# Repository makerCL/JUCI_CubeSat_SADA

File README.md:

## CubeSat Solar Array Drive - Cal Poly Senior Project

This repository presents the development and proposed design of a deployable Solar Array Drive Assembly that could be flown on space-bound CubeSat missions. Our project addresses the need for reliable sources of power in spacecraft and other missions beyond the Earth's atmosphere. Our goal is to create a two degree of freedom SADA, including the passive retainment, deployment, and axial rotation of a solar array to track the sun during the CubeSat’s orbit. It will have the ability to be easily adapted and integrated into other CubeSat builds but does not include other subsystems necessary for full satellite. The scope includes three main areas: the design and manufacture of a 90-degree locking hinge that allows multiple solar arrays to deploy from the stored launch state, the controlled axial rotation of the deployed panels, and the electronics necessary to manage these features with the potential for sun tracking algorithms. 

Subsystem Managers:
- Miles - Electronics
- Gavin - Software
- James - Project Management
- Kory  - Mechanical
- Jose  - Mechanical

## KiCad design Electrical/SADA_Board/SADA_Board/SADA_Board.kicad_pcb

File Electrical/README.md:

This file details the electrical subsystems
Author: Miles Alderman

##Boards:
- Photodiode Breakout: used for sun sensing with one connected to each solar array
- Pico Shield: Peripherals and connection points that interfaces with a Raspberry Pi Pico

##Accessing the Files
- all project files are in Kicad version 6, which the use will need to use to view them
- Digikey library was imported, available at https://forum.digikey.com/t/importing-the-digi-key-kicad-library-into-kicad-5-0-0/4075
- Custom schematic symbols and footprints are in the "KiCad Libs" folder. These will need to be imported

#SADA Board

##Description
The "SADA BOARD" encompasses all the functionality necessary for the Solar Array Drive Assembly and its components. It would interface with a "Systems Board" through a protocol like I2C or CAN.

##Functionality
- Voltage regulator accepts between 3.7 to 4.2V from an external power supply, which represents a single parallel group of Lithium Ion cells, as would like be present in a CubeSat since about 66% of nano and pico scale satellites implement them.(Bouwmeester and Guo). A battery and battery management system is out of scope for this project.
- Nichrome Wire burner: to burn the fishing line that passively retains the spring-loaded solar arrays, we use Nichrome burn wire. This is necessary since the satellite must be powered off during launch. There are pins used to control the burn signal, one of which is the enable for the PMIC, the other of which controls a Mosfet for connecting power to the Nichrome. In some tests, we found that when the system was powered up from its launch state, if the power supply was turned on with a direct connection to the wire it heated it slower, resulting in less reliable deployment. By having a transistor, we can allow the PMIC to become fully stable, and then open it to heat the wire. This PMIC can then be disable to save power after the wire is burnt. Our tests foudn that about 1.5A was the minimum current to heat the wire enough to cleanly burn the fishing line.
- Attitude Determination Diodes: since in a full CubeSat build there would need to be orientation photodiodes on each corner, the peripherals are provided to do so. This includes a MUX to an ADC channel of the MCU to take this measurement.
    - The photodiodes were connected in reverse bias to the inverting input of an op amp. To take a reading with good resolution, this tiny current must be amplified before reaching an ADC. Transconductance amplifiers are a way to do this, connecting the photodiode to the inverting input of an op-amp, the non-inverting input to ground, and placing a feedback resistor from inverting input to output. A capacitor in parallel with the feedback resistor adds stability by acting as a voltage buffer. Capacitance in the photodiode combined with the feedback resistor naturally create a low pass filter as well. The output voltage of the amplifier can then be connected to an ADC channel of the MCU. The voltage sent to the ADC channel is equal to the photodiode current times the feedback resistor plus the offset voltage at the non-inverting input.
    - It is important to verify the photodiode current is at least an order of magnitude more than the input bias current of the op amp, which roughly doubles with ever 10 deg C increase in temperature.
- Stepper Motor Drivers: Since the stepper motors for axial rotation of the arrays need to be driven from the MCU, a Darlington Transistor array is used to accomplish this. This allows the small current of the MCU GPIO to drive the much higher current needed by a stepper, taken from the 5V supply. Stepper motors are precise, but very power hungry due to _________, so we decided to have MOSFETS that can disconnect from power for when the steppers are not actively changed. This does eliminate some functionality of the steppers, such as fractional stepping, but the resolution of that is far greater than our sensing method's, and thus we couldn't take advantage of it anywyas.
- Breakout board connectors: connectors to the Photodiode Breakout Board are implemented for 2 MUX pins, an ADC channel, power and ground

##Design Considerations 
For full information, please see current design report in the parent folder of the repository. Some key details are listed below
- Were not able to use a "space grade" MCU since they are far too expensive for the price point of this project. We therefore are trying to adapt consumer grade MCUs to fit the needs of this project. This would only protect against total radiation experienced from low energy particles, and not against bit flips. In the systems board, TMR would likely be used. 
- Since this is a prototype and will not be launched into space, we aren't going through the rad hardening. It would be silly to spend extra money for a more specific MCU that wouldn’t work anyways. All the other common MCUs have similar temperature ranges besides the ESP32, although its is still not within range of what we expect a CubeSat to encounter
- Dual Modular Redundancy for these systems?
- In a full system, the battery system would output between about 3.6 - 4.2V if a lithium ion cell chemistry was used. We need to step that down to 3.3V for the RP2040. We chose to use an LDO to power the MCU despite them being less efficient than switching regulators since when the LDOs will use less power when considering the high amount of sleep time of the MCU.
- We decided to use stepper motors despite them being very power hungry. Stepper motors invert  the "locked rotor" issue of dc motors, stepping between locked rotor positions. This means that when the motor is not moving, the coils are still fully energized. This is bad for a CubeSat, where power is extremely scarce. To get around this issue while still utilizing the positional accuracy of stepper motors, we can step the motor and then immediately disconnect the power line so that it stops drawing current. Since the cores of the motor are permenant magnets, the motor remains in the last position even when the motor is off, as long as we do not depend on any partial-stepping functions. 
- USB implemented for the development process, but isn't necessary on a deployed system. It allows the engineer to set it up as a flash device, making it convenient to interface with. The STLINK with SWD and TX/RX pins can be used for all of the functionality in its absence as well. It enables debugging, a serial port, and flashing binary code (such as Micropython) onto the main board.
- The stepper driver boost converters were designed to be able to handle a maximum current of 1A. The stepper motor 28BYJ-48 chosen has a maximum current of approximately 0.28A, so this means that one boost converter could drive 2 motors with a safety factor of 2. This current can easily be increased with minor changes in the supporting circuitry found in the datasheet for the boost converter.
- The darlington transistors were abandoned. They are 45 year old tech, they have pretty substantial current to drive it (power hunger), they have a more substantial voltage drop. Stepper driver chips are much more efficient. 
- Stepper motors were eventually abandoned in favor of a BLDC. https://llis.nasa.gov/lesson/893
- 

SOFTWARE
- NRST Pin exposed to systems board so that software reflash could be triggered externally and passed through I2C instead of SWD. On our board though, we still have teh SWD pins exposed since that is how we will be flashing code. NRST is also helpful as an external reset as it resets the registers and changes the program counter to the reset vector. https://electronics.stackexchange.com/questions/491068/what-is-the-use-of-nrst-pin-in-stm32f401rct6 and p21 of Data sheet

##Citations:
1. J. Bouwmeester, J. Guo, Survey of worldwide pico- and nanosatellite missions, distributions and subsystem technology, Acta Astronautica,
2.  https://www.analog.com/en/technical-articles/optimizing-precision-photodiode-sensor-circuit-design.html

CONCERNS:
- Auxillary photodiode board- if it's just on the panel, it likely will be buffeted with radiation, heat, etc. Need to plan for this

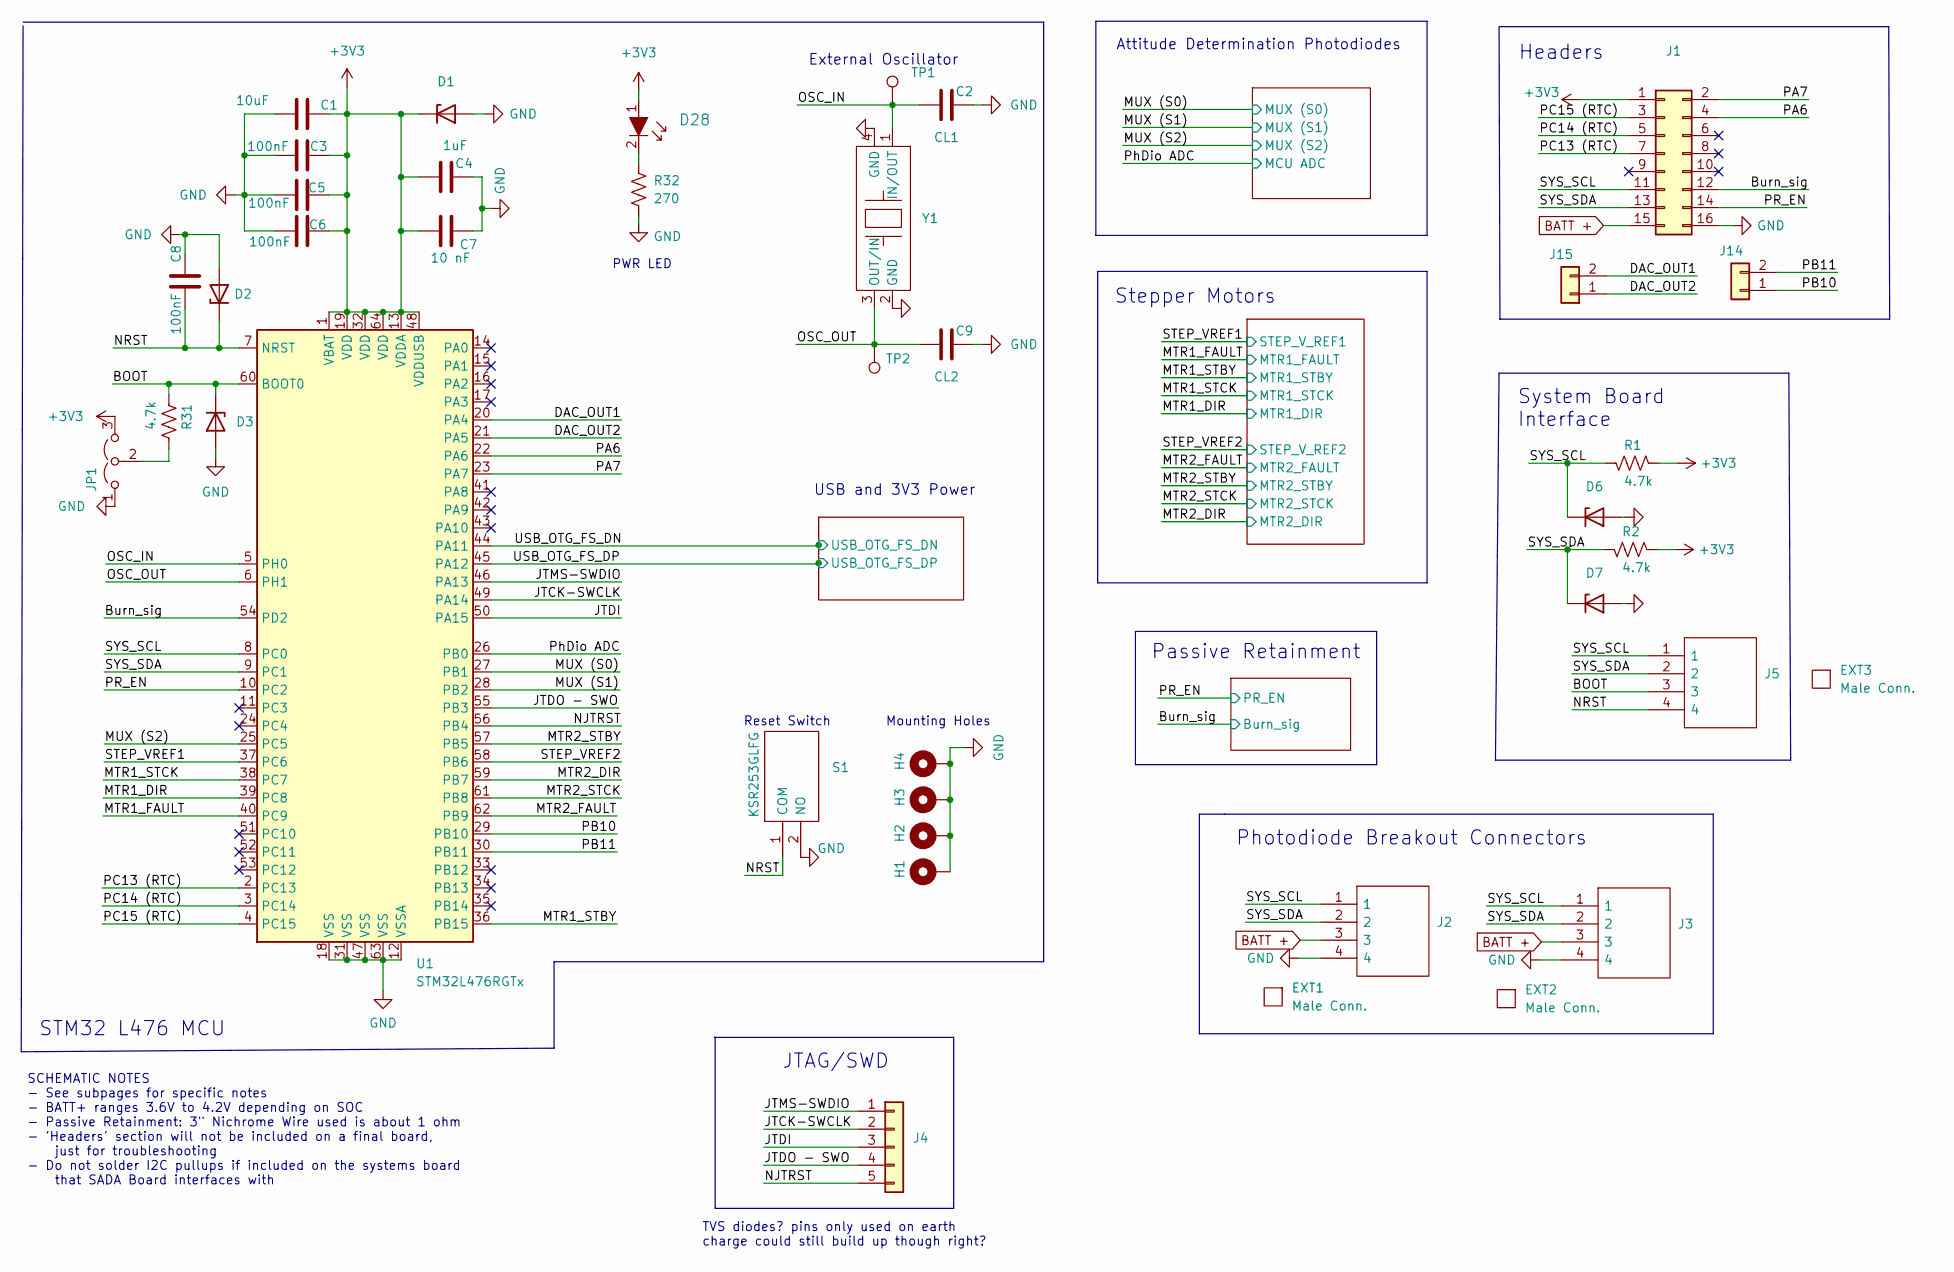
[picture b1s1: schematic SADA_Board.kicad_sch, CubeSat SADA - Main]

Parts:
C1: 10uF; C_0603_1608Metric; MPN F981A106MMUAJ6
C2: CL1; C_0402_1005Metric; MPN CGA2B2C0G1H060D050BA
C3, C5, C6, C8: 100nF; C_0402_1005Metric; MPN GRT155R71C104KE01J
C4: 1uF; C_0603_1608Metric; MPN TACL105K016XTA
C7: 10 nF; C_0402_1005Metric; MPN GRT155R71C103KE01J
C9: CL2; C_0402_1005Metric; MPN CGA2B2C0G1H060D050BA
D1, D2, D3, D6, D7: TVS; D_0402_1005Metric; MPN ESD321DPYR
D28: LTST-C193KRKT-5A; LED_0603_1608Metric; MPN LTST-C193KRKT-5A
EXT1, EXT2, EXT3: Male Conn.; EXT_no_footprint; MPN 0014562042
H1, H2, H3, H4: MountingHole_Pad; MountingHole_2.5mm_Pad
J1: Conn_02x08_Odd_Even; PinHeader_2x08_P2.00mm_Vertical; MPN 3-1734506-1
J2, J3, J5: 70543-0108; SHDR4W64P0X254_1X4_1271X508X1181P; Mouser Part Number 538-70543-0108
J4: Conn_01x05; PinHeader_1x05_P2.00mm_Vertical_SMD_Pin1Left; MPN 2PH1-10-UA-SMT-A
J14, J15: Conn_01x02; PinSocket_1x02_P2.00mm_Vertical
JP1: Jumper_3_Open; PinHeader_1x03_P2.00mm_Vertical; MPN 2PH1-10-UA-SMT-A
R1, R2, R31: 4.7k; R_0402_1005Metric; MPN AC0402FR-134K7L
R32: 270; R_0402_1005Metric; MPN CRGCQ0402F270R
S1: KSR253GLFG; Mouser Part Number 611-KSR253G-LFG
TP1, TP2: TestPoint; TestPoint_Pad_D1.0mm
U1: STM32L476RGTx; LQFP-64_10x10mm_P0.5mm; MPN STM32L476RGT3
Y1: ECS_Chrystal_; XTAL_ECS-160-8-36Q-AES-TR; MPN ECS-160-8-36Q-AES-TR

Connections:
+3V3: C1.1, C3.2, C4.2, C5.2, C6.2, C7.2, D1.1 (K), D28.1, J1.1, JP1.3 (B), R1.1, R2.1, U1.1 (VBAT), U1.13 (VDDA), U1.19 (VDD), U1.32 (VDD), U1.48 (VDDUSB), U1.64 (VDD); also elsewhere on the board
/BOOT: D3.1 (K), J5.3, R31.1, U1.60 (BOOT0)
/Burn_sig: J1.12, U1.54 (PD2); also elsewhere on the board
/DAC_OUT1: J15.2, U1.20 (PA4)
/DAC_OUT2: J15.1, U1.21 (PA5)
/JTCK-SWCLK: J4.2, U1.49 (PA14)
/JTDI: J4.3, U1.50 (PA15)
/JTDO - SWO: J4.4, U1.55 (PB3)
/JTMS-SWDIO: J4.1, U1.46 (PA13)
/MTR1_DIR: U1.39 (PC8); also elsewhere on the board
/MTR1_FAULT: U1.40 (PC9); also elsewhere on the board
/MTR1_STBY: U1.36 (PB15); also elsewhere on the board
/MTR1_STCK: U1.38 (PC7); also elsewhere on the board
/MTR2_DIR: U1.59 (PB7); also elsewhere on the board
/MTR2_FAULT: U1.62 (PB9); also elsewhere on the board
/MTR2_STBY: U1.57 (PB5); also elsewhere on the board
/MTR2_STCK: U1.61 (PB8); also elsewhere on the board
/MUX (S0): U1.27 (PB1); also elsewhere on the board
/MUX (S1): U1.28 (PB2); also elsewhere on the board
/MUX (S2): U1.25 (PC5); also elsewhere on the board
/NJTRST: J4.5, U1.56 (PB4)
/NRST: C8.2, D2.1 (K), J5.4, S1.1 (COM), U1.7 (NRST)
/OSC_IN: C2.2, TP1.1, U1.5 (PH0), Y1.1 (IN/OUT)
/OSC_OUT: C9.2, TP2.1, U1.6 (PH1), Y1.3 (OUT/IN)
/PA6: J1.4, U1.22 (PA6)
/PA7: J1.2, U1.23 (PA7)
/PB10: J14.1, U1.29 (PB10)
/PB11: J14.2, U1.30 (PB11)
/PC13 (RTC): J1.7, U1.2 (PC13)
/PC14 (RTC): J1.5, U1.3 (PC14)
/PC15 (RTC): J1.3, U1.4 (PC15)
/PR_EN: J1.14, U1.10 (PC2); also elsewhere on the board
/PhDio ADC: U1.26 (PB0); also elsewhere on the board
/STEP_VREF1: U1.37 (PC6); also elsewhere on the board
/STEP_VREF2: U1.58 (PB6); also elsewhere on the board
/SYS_SCL: D6.1 (K), J1.11, J2.1, J3.1, J5.1, R1.2, U1.8 (PC0)
/SYS_SDA: D7.1 (K), J1.13, J2.2, J3.2, J5.2, R2.2, U1.9 (PC1)
/USB_OTG_FS_DN: U1.44 (PA11); also elsewhere on the board
/USB_OTG_FS_DP: U1.45 (PA12); also elsewhere on the board
BATT +: J1.15, J2.3, J3.3; also elsewhere on the board
GND: C1.2, C2.1, C3.1, C4.1, C5.1, C6.1, C7.1, C8.1, C9.1, D1.2 (A), D2.2 (A), D3.2 (A), D6.2 (A), D7.2 (A), H1.1, H2.1, H3.1, H4.1, J1.16, J2.4, J3.4, JP1.1 (A), R32.2, S1.2 (NO), U1.12 (VSSA), U1.18 (VSS), U1.31 (VSS), U1.47 (VSS), U1.63 (VSS), Y1.2 (GND), Y1.4 (GND); also elsewhere on the board
unnamed: D28.2, R32.1
unnamed: JP1.2 (C), R31.2

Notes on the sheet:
SCHEMATIC NOTES - See subpages for specific notes - BATT+ ranges 3.6V to 4.2V depending on SOC - Passive Retainment: 3" Nichrome Wire used is about 1 ohm - 'Headers' section will not be included on a final board, just for troubleshooting - Do not solder I2C pullups if included on the systems board 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
TVS diodes? pins only used on earth charge could still build up though right?
Reset Switch
Stepper Motors
Photodiode Breakout Connectors
STM32 L476 MCU
Mounting Holes
Attitude Determination Photodiodes
External Oscillator
JTAG/SWD
Passive Retainment
Headers
PWR LED
System Board Interface
USB and 3V3 Power

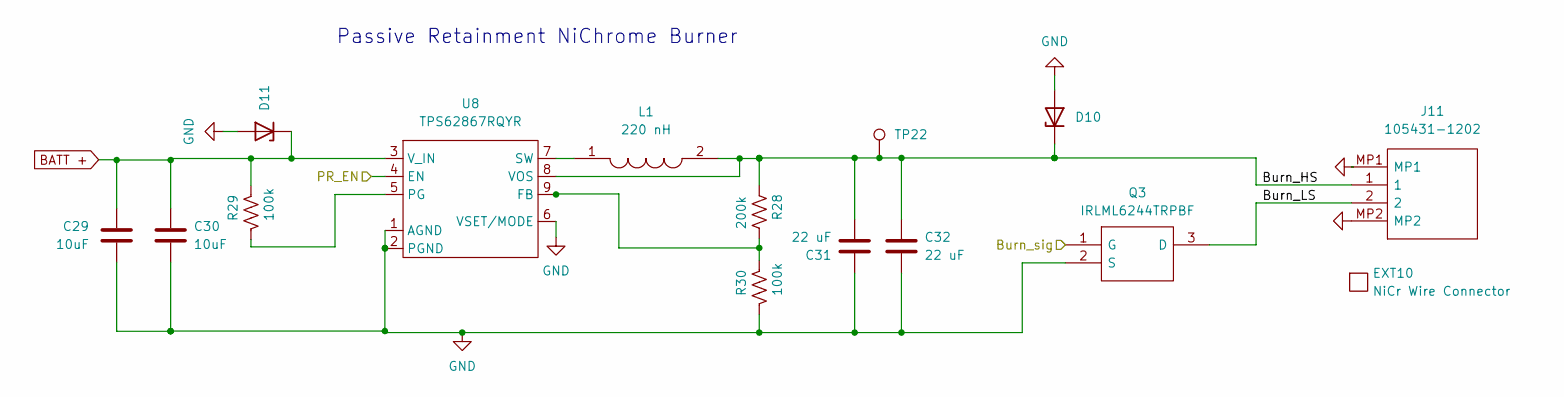
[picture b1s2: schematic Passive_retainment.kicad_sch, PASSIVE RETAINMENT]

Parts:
C29, C30: 10uF; C_0603_1608Metric; MPN GRT188C81A106ME13D
C31, C32: 22 uF; C_1210_3225Metric; MPN CGA6P1X7R1C226M250AC
D10, D11: TVS; D_0402_1005Metric
EXT10: NiCr Wire Connector; EXT_no_footprint; MPN 3-640427-2
J11: 105431-1202; 1054311202; Mouser Part Number 538-105431-1202
L1: 220 nH; INDPM3630X150N; Mouser Part Number 70-IHLP1212AEERR22M1
Q3: IRLML6244TRPBF; SOT95P237X112-3N; Mouser Part Number 942-IRLML6244TRPBF
R28: 200k; R_0603_1608Metric_Pad0.98x0.95mm_HandSolder; MPN AC0603FR-07200KL
R29, R30: 100k; R_0402_1005Metric; MPN RMCF0402FT100K
TP22: TestPoint; TestPoint_Pad_D1.0mm
U8: TPS62867RQYR; VQFN-9; MPN TPS62867RQYR

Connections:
/Burn_sig: Q3.1 (G); also elsewhere on the board
/PR_EN: U8.4 (EN); also elsewhere on the board
/Passive Retainment/Burn_HS: C31.2, C32.1, D10.1 (K), J11.1, L1.2, R28.1, TP22.1, U8.8 (VOS)
/Passive Retainment/Burn_LS: J11.2, Q3.3 (D)
BATT +: C29.2, C30.1, D11.1 (K), R29.1, U8.3 (V_IN); also elsewhere on the board
GND: C29.1, C30.2, C31.1, C32.2, D10.2 (A), D11.2 (A), J11.MP1, J11.MP2, Q3.2 (S), R30.2, U8.1 (AGND), U8.2 (PGND), U8.6 (VSET/MODE); also elsewhere on the board
unnamed: L1.1, U8.7 (SW)
unnamed: R28.2, R30.1, U8.9 (FB)
unnamed: R29.2, U8.5 (PG)

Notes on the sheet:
Passive Retainment NiChrome Burner

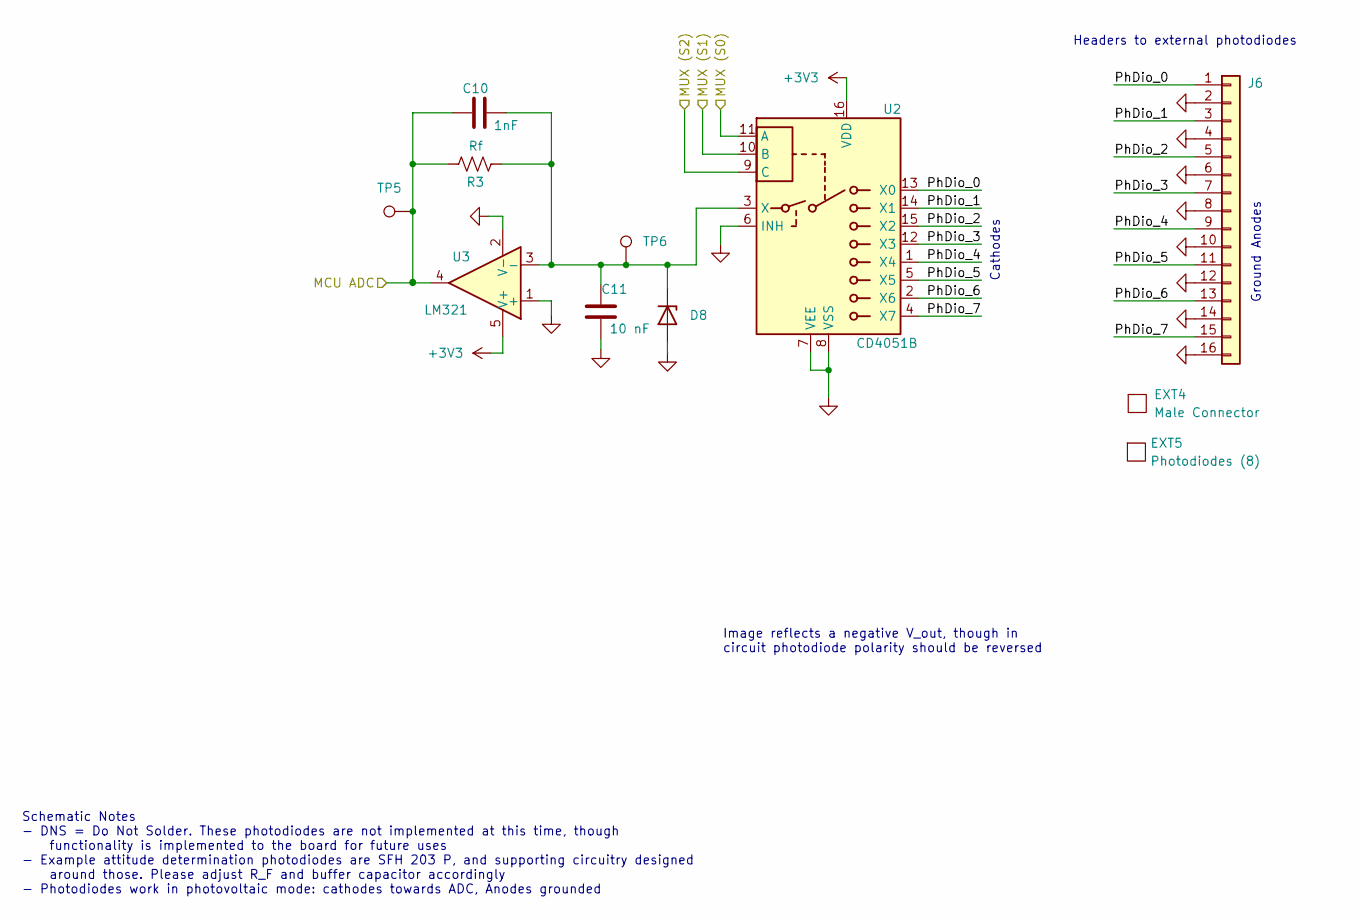
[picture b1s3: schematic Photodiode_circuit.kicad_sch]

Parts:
C10: 1nF; R_0402_1005Metric; MPN GCM155R71H102KA37J
C11: 10 nF; C_0402_1005Metric; MPN GRT155R71C103KE01J
D8: TVS; D_0402_1005Metric
EXT4: Male Connector; EXT_no_footprint; MPN 1-353293-6
EXT5: Photodiodes (8); EXT_no_footprint; MPN SFH 203 P
J6: Conn_01x16; CON16_1X16_DUH_HPI125_TYC; MPN 1-292230-6
R3: 200k; R_0603_1608Metric_Pad0.98x0.95mm_HandSolder; MPN AC0603FR-07200KL
TP5, TP6: TestPoint; TestPoint_Pad_D1.0mm
U2: CD4051B; PW0016A_L; MPN CD4051BQPWRG4Q1
U3: LM321; SOT-23-5; MPN LM321LVIDBVR

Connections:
+3V3: U2.16 (VDD), U3.5 (V+); also elsewhere on the board
/CRNR PHOTODIODES/PhDio_0: J6.1, U2.13 (X0)
/CRNR PHOTODIODES/PhDio_1: J6.3, U2.14 (X1)
/CRNR PHOTODIODES/PhDio_2: J6.5, U2.15 (X2)
/CRNR PHOTODIODES/PhDio_3: J6.7, U2.12 (X3)
/CRNR PHOTODIODES/PhDio_4: J6.9, U2.1 (X4)
/CRNR PHOTODIODES/PhDio_5: J6.11, U2.5 (X5)
/CRNR PHOTODIODES/PhDio_6: J6.13, U2.2 (X6)
/CRNR PHOTODIODES/PhDio_7: J6.15, U2.4 (X7)
/MUX (S0): U2.11 (A); also elsewhere on the board
/MUX (S1): U2.10 (B); also elsewhere on the board
/MUX (S2): U2.9 (C); also elsewhere on the board
/PhDio ADC: U3.4; also elsewhere on the board
GND: C11.2, D8.2 (A), J6.2, J6.4, J6.6, J6.8, J6.10, J6.12, J6.14, J6.16, U2.6 (INH), U2.7 (VEE), U2.8 (VSS), U3.1 (+), U3.2 (V-); also elsewhere on the board
unnamed: C10.1, R3.2, TP5.1
unnamed: C10.2, C11.1, D8.1 (K), R3.1, TP6.1, U2.3 (X), U3.3 (-)

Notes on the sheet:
Headers to external photodiodes
Image reflects a negative V_out, though in circuit photodiode polarity should be reversed
Cathodes
Ground Anodes
Schematic Notes - DNS = Do Not Solder. These photodiodes are not implemented at this time, though functionality is implemented to the board for future uses - Example attitude determination photodiodes are SFH 203 P, and supporting circuitry designed around those. Please adjust R_F and buffer capaci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

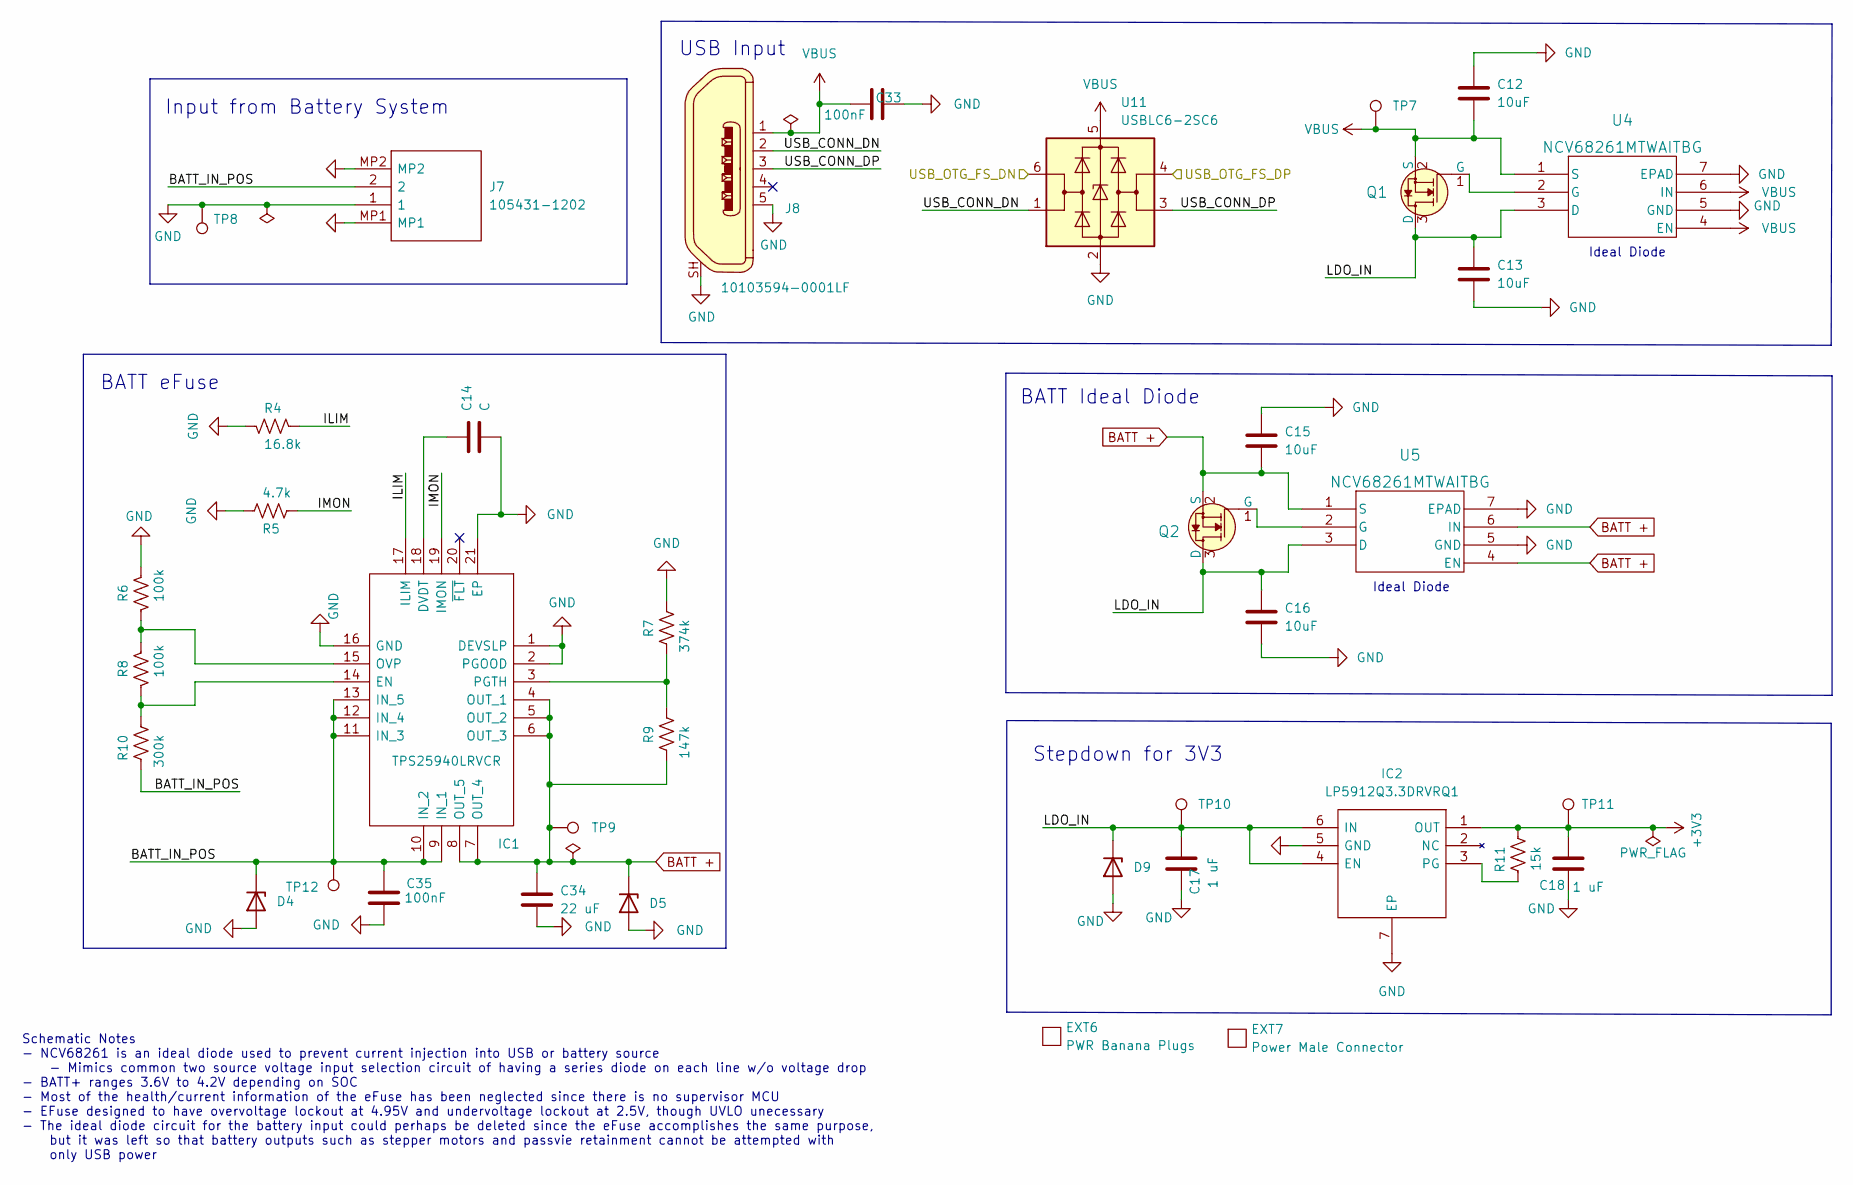
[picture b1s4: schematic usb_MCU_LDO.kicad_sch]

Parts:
C12, C13, C15, C16: 10uF; C_0603_1608Metric; MPN GRT188C81A106ME13D
C14: C; C_0402_1005Metric; MPN CC0402KRX7R7BB152
C17, C18: 1 uF; C_0603_1608Metric; MPN TACL105K016XTA
C33, C35: 100nF; C_0402_1005Metric; MPN GRT155R71C104KE01J
C34: 22 uF; C_1210_3225Metric; MPN CGA6P1X7R1C226M250AC
D4, D5, D9: TVS; D_0402_1005Metric; MPN ESD321DPYR
EXT6: PWR Banana Plugs; EXT_no_footprint; MPN 1325-02
EXT7: Power Male Connector; EXT_no_footprint; MPN 3-640427-2
IC1: TPS25940LRVCR; QFN50P300X400X80-21N; Mouser Part Number 595-TPS25940LRVCR
IC2: LP5912Q3.3DRVRQ1; SON65P200X200X80-7N; Mouser Part Number 595-LP5912Q3.3DRVRQ1
J7: 105431-1202; 1054311202; Mouser Part Number 538-105431-1202
J8: 10103594-0001LF; USB_Micro_B_Female_10103594-0001LF; MPN 10103594-0001LF; Digi-Key_PN 609-4050-1-ND
Q1, Q2: NVR5198NLT1G; SOT-23-3; MPN NVR5198NLT1G
R4: 16.8k; R_0402_1005Metric; MPN AC0402FR-0716K9L
R5: 4.7k; R_0402_1005Metric; MPN AC0402FR-134K7L
R6, R8: 100k; R_0402_1005Metric; MPN RMCF0402FT100K
R7: 374k; R_0402_1005Metric; MPN RC0402FR-07374KL
R9: 147k; R_0402_1005Metric; MPN RC0402FR-07147KL
R10: 300k; R_0402_1005Metric; MPN RC0402JR-07300KL
R11: 15k; R_0603_1608Metric; MPN AC0603FR-0715KL
TP7, TP8, TP9, TP10, TP11, TP12: TestPoint; TestPoint_Pad_D1.0mm
U4, U5: NCV68261MTWAITBG; WDFNW6_511DW_ONS_OSI; MPN NCV68261MTWAITBG
U11: USBLC6-2SC6; SOT-23-6

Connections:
+3V3: C18.2, IC2.1 (OUT), R11.2, TP11.1; also elsewhere on the board
/USB and MCU LDO/BATT_IN_POS: C35.2, D4.1 (K), IC1.9 (IN_1), IC1.10 (IN_2), IC1.11 (IN_3), IC1.12 (IN_4), IC1.13 (IN_5), J7.2, R10.1, TP12.1
/USB and MCU LDO/ILIM: IC1.17 (ILIM), R4.1
/USB and MCU LDO/IMON: IC1.19 (IMON), R5.1
/USB and MCU LDO/LDO_IN: C13.1, C16.1, C17.2, D9.1 (K), IC2.4 (EN), IC2.6 (IN), Q1.3 (D), Q2.3 (D), TP10.1, U4.3 (D), U5.3 (D)
/USB and MCU LDO/USB_CONN_DN: J8.2, U11.1 (I/O1)
/USB and MCU LDO/USB_CONN_DP: J8.3, U11.3 (I/O2)
/USB_OTG_FS_DN: U11.6 (I/O1); also elsewhere on the board
/USB_OTG_FS_DP: U11.4 (I/O2); also elsewhere on the board
BATT +: C15.2, C34.1, D5.1 (K), IC1.4 (OUT_1), IC1.5 (OUT_2), IC1.6 (OUT_3), IC1.7 (OUT_4), IC1.8 (OUT_5), Q2.2 (S), R9.1, TP9.1, U5.1 (S), U5.4 (EN), U5.6 (IN); also elsewhere on the board
GND: C12.1, C13.2, C14.2, C15.1, C16.2, C17.1, C18.1, C33.2, C34.2, C35.1, D4.2 (A), D5.2 (A), D9.2 (A), IC1.1 (DEVSLP), IC1.2 (PGOOD), IC1.16 (GND), IC1.21 (EP), IC2.5 (GND), IC2.7 (EP), J7.1, J7.MP1, J7.MP2, J8.5, J8.SH, R4.2, R5.2, R6.1, R7.2, TP8.1, U4.5 (GND), U4.7 (EPAD), U5.5 (GND), U5.7 (EPAD), U11.2 (GND); also elsewhere on the board
unnamed: C14.1, IC1.18 (DVDT)
unnamed: IC1.3 (PGTH), R7.1, R9.2
unnamed: IC1.14 (EN), R8.2, R10.2
unnamed: IC1.15 (OVP), R6.2, R8.1
unnamed: IC2.3 (PG), R11.1
unnamed: Q1.1 (G), U4.2 (G)
unnamed: Q2.1 (G), U5.2 (G)
VBUS: C12.2, C33.1, J8.1, Q1.2 (S), TP7.1, U4.1 (S), U4.4 (EN), U4.6 (IN), U11.5 (VBUS)

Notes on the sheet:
Ideal Diode
BATT eFuse
Input from Battery System
Schematic Notes - NCV68261 is an ideal diode used to prevent current injection into USB or battery source - Mimics common two source voltage input selection circuit of having a series diode on each line w/o voltage drop - BATT+ ranges 3.6V to 4.2V depending on SOC - Most of the health/current infor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
Stepdown for 3V3
BATT Ideal Diode
USB Input

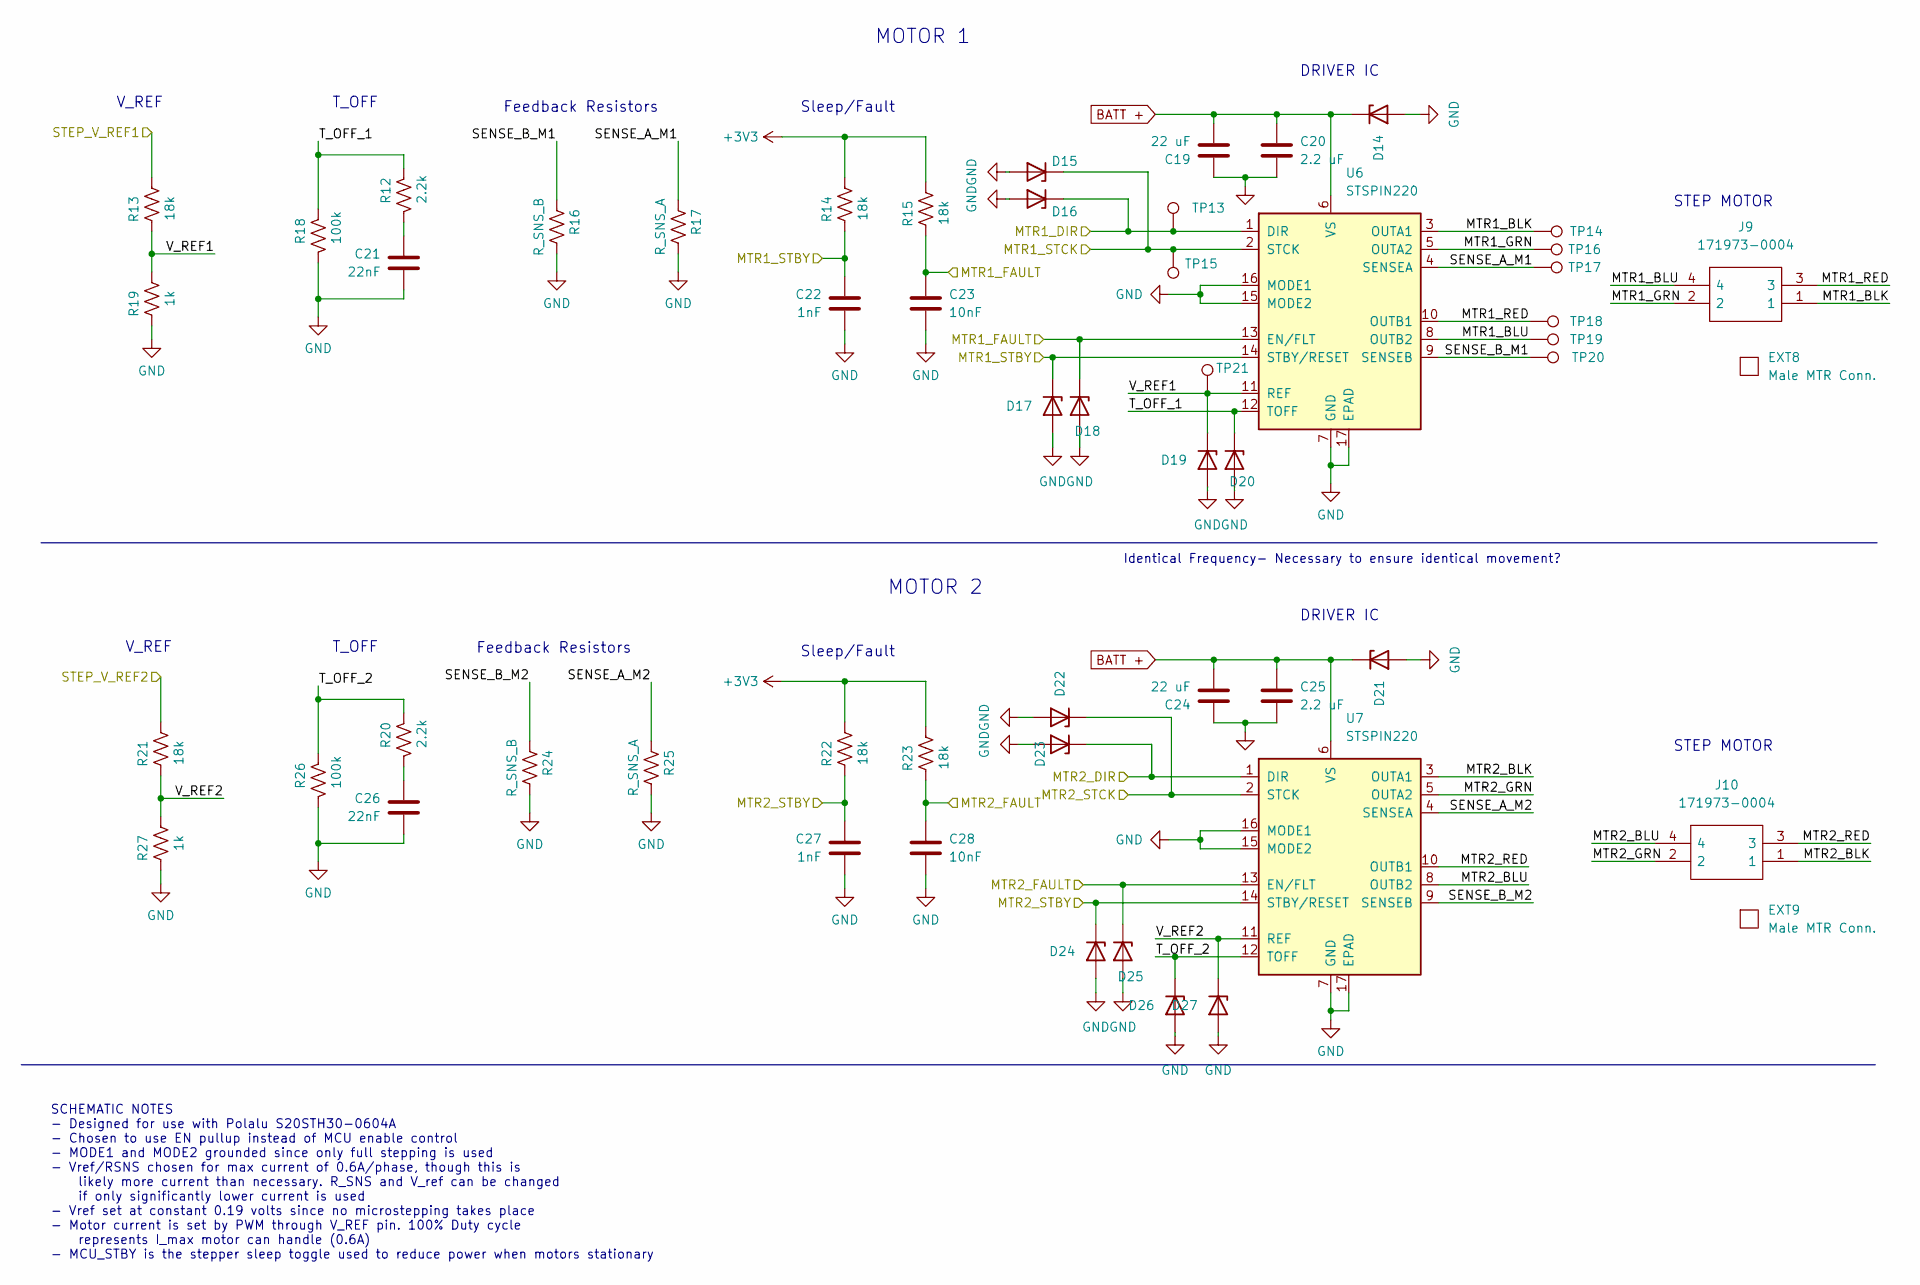
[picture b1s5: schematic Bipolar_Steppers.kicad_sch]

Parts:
C19, C24: 22 uF; C_1210_3225Metric; MPN CGA6P1X7R1C226M250AC
C20, C25: 2.2 uF; R_0603_1608Metric; MPN CGA3E1X7S1C225M080AC
C21, C26: 22nF; C_0402_1005Metric; MPN AC0402KRX7R7BB223
C22, C27: 1nF; R_0402_1005Metric; MPN GCM155R71H102KA37J
C23, C28: 10nF; R_0402_1005Metric; MPN GRT155R71C103KE01J
D14, D15, D16, D17, D18, D19, D20, D21, D22, D23, D24, D25, D26, D27: TVS; D_0402_1005Metric
EXT8, EXT9: Male MTR Conn.; EXT_no_footprint; MPN 0014562042
J9, J10: 171973-0004; 1719730004; Mouser Part Number 538-171973-0004
R12, R20: 2.2k; R_0402_1005Metric; MPN AC0402FR-072K2L
R13, R14, R15, R21, R22, R23: 18k; R_0402_1005Metric; MPN AC0402FR-0718KL
R16, R17, R24, R25: 330m; R_1206_3216Metric; MPN KRL1632E-M-R330-F-T5
R18, R26: 100k; R_0402_1005Metric; MPN RMCF0402FT100K
R19, R27: 1k; R_0402_1005Metric; MPN AC0402FR-131KL
TP13, TP14, TP15, TP16, TP17, TP18, TP19, TP20, TP21: TestPoint; TestPoint_Pad_D1.0mm
U6, U7: STSPIN220; VQFN-16-1EP_3x3mm_P0.5mm_EP1.8x1.8mm; MPN STSPIN220

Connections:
+3V3: R14.2, R15.2, R22.2, R23.2; also elsewhere on the board
/MTR1_DIR: D16.1 (K), TP13.1, U6.1 (DIR); also elsewhere on the board
/MTR1_FAULT: C23.1, D18.1 (K), R15.1, U6.13 (EN/FLT); also elsewhere on the board
/MTR1_STBY: C22.1, D17.1 (K), R14.1, U6.14 (STBY/RESET); also elsewhere on the board
/MTR1_STCK: D15.1 (K), TP15.1, U6.2 (STCK); also elsewhere on the board
/MTR2_DIR: D23.1 (K), U7.1 (DIR); also elsewhere on the board
/MTR2_FAULT: C28.1, D25.1 (K), R23.1, U7.13 (EN/FLT); also elsewhere on the board
/MTR2_STBY: C27.1, D24.1 (K), R22.1, U7.14 (STBY/RESET); also elsewhere on the board
/MTR2_STCK: D22.1 (K), U7.2 (STCK); also elsewhere on the board
/STEP_VREF1: R13.2; also elsewhere on the board
/STEP_VREF2: R21.2; also elsewhere on the board
/Steppers /MTR1_BLK: J9.1, TP14.1, U6.3 (OUTA1)
/Steppers /MTR1_BLU: J9.4, TP19.1, U6.8 (OUTB2)
/Steppers /MTR1_GRN: J9.2, TP16.1, U6.5 (OUTA2)
/Steppers /MTR1_RED: J9.3, TP18.1, U6.10 (OUTB1)
/Steppers /MTR2_BLK: J10.1, U7.3 (OUTA1)
/Steppers /MTR2_BLU: J10.4, U7.8 (OUTB2)
/Steppers /MTR2_GRN: J10.2, U7.5 (OUTA2)
/Steppers /MTR2_RED: J10.3, U7.10 (OUTB1)
/Steppers /SENSE_A_M1: R17.1, TP17.1, U6.4 (SENSEA)
/Steppers /SENSE_A_M2: R25.1, U7.4 (SENSEA)
/Steppers /SENSE_B_M1: R16.1, TP20.1, U6.9 (SENSEB)
/Steppers /SENSE_B_M2: R24.1, U7.9 (SENSEB)
/Steppers /T_OFF_1: D20.1 (K), R12.1, R18.1, U6.12 (TOFF)
/Steppers /T_OFF_2: D26.1 (K), R20.1, R26.1, U7.12 (TOFF)
/Steppers /V_REF1: D19.1 (K), R13.1, R19.2, TP21.1, U6.11 (REF)
/Steppers /V_REF2: D27.1 (K), R21.1, R27.2, U7.11 (REF)
BATT +: C19.2, C20.1, C24.2, C25.1, D14.1 (K), D21.1 (K), U6.6 (VS), U7.6 (VS); also elsewhere on the board
GND: C19.1, C20.2, C21.2, C22.2, C23.2, C24.1, C25.2, C26.2, C27.2, C28.2, D14.2 (A), D15.2 (A), D16.2 (A), D17.2 (A), D18.2 (A), D19.2 (A), D20.2 (A), D21.2 (A), D22.2 (A), D23.2 (A), D24.2 (A), D25.2 (A), D26.2 (A), D27.2 (A), R16.2, R17.2, R18.2, R19.1, R24.2, R25.2, R26.2, R27.1, U6.7 (GND), U6.15 (MODE2), U6.16 (MODE1), U6.17 (EPAD), U7.7 (GND), U7.15 (MODE2), U7.16 (MODE1), U7.17 (EPAD); also elsewhere on the board
unnamed: C21.1, R12.2
unnamed: C26.1, R20.2

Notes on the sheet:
Identical Frequency- Necessary to ensure identical movement?
Feedback Resistors
DRIVER IC
T_OFF
Sleep/Fault
MOTOR 1
STEP MOTOR
MOTOR 2
V_REF
SCHEMATIC NOTES - Designed for use with Polalu S20STH30-0604A - Chosen to use EN pullup instead of MCU enable control - MODE1 and MODE2 grounded since only full stepping is used - Vref/RSNS chosen for max current of 0.6A/phase, though this is likely more current than necessary. R_SNS and V_ref can 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

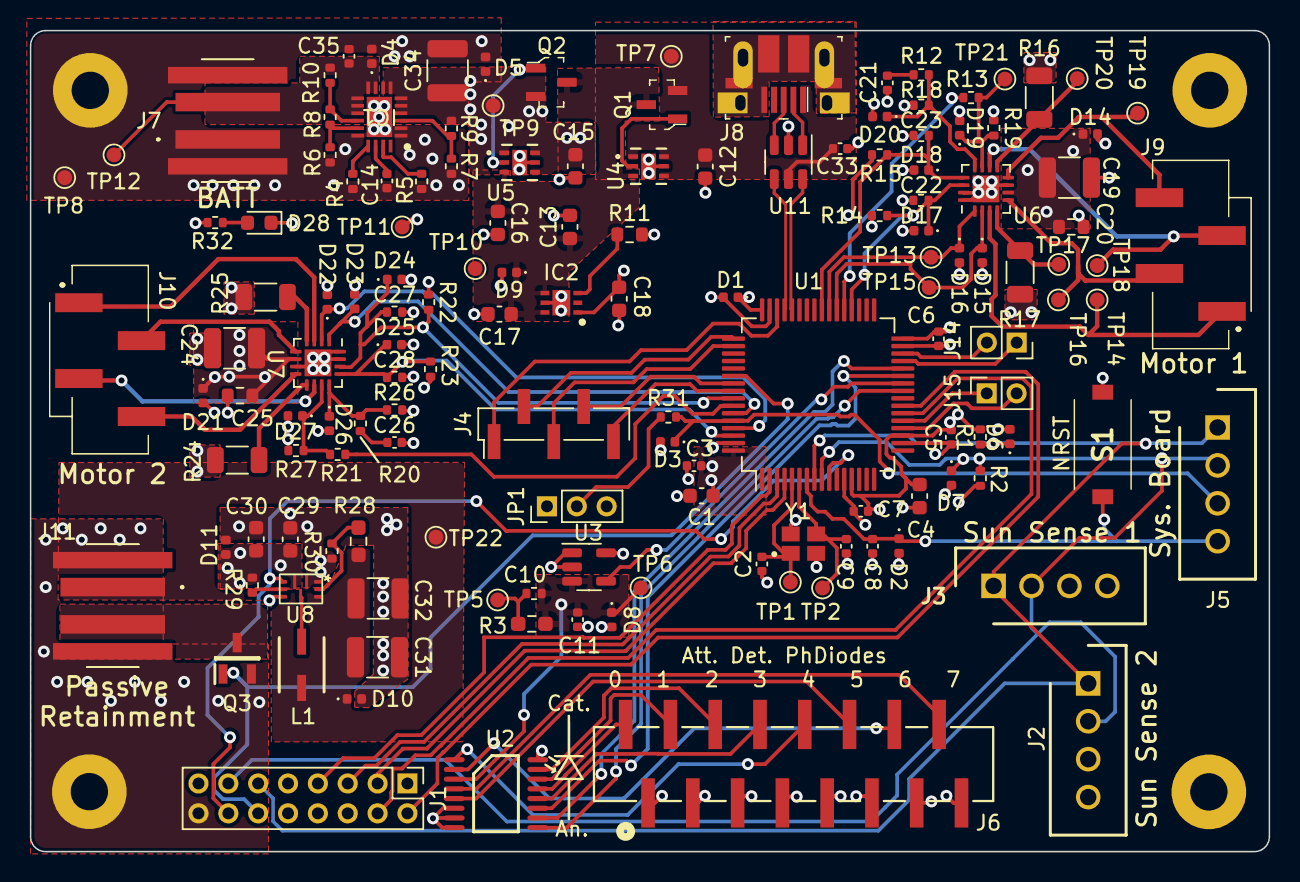
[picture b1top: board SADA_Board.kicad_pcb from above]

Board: 4 copper layers, 83.0 x 55.0 mm, 158 parts (0 on the bottom side), 90 nets.

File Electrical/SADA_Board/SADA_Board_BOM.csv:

Item,Qty,QTY for 3,Reference(s),Value,MPN
1,7,42,"C1, C12, C13, C15, C16, C29, C30",10uF,F981A106MMUAJ6
2,2,12,"C2, C9",CL1,CGA2B2C0G1H060D050BA
3,6,36,"C3, C5, C6, C8, C33, C35",100nF,GRT155R71C104KE01J
4,1,6,C4,1uF,TACL105K016XTA
5,2,12,"C7, C11",10 nF,GRT155R71C103KE01J
7,3,18,"C10, C22, C27",1nF,GCM155R71H102KA37J
8,1,6,C14,C,CC0402KRX7R7BB152
9,2,12,"C17, C18",1 uF,TACL105K016XTA
10,5,30,"C19, C24, C31, C32, C34",22 uF,CGA6P1X7R1C226M250AC
11,2,12,"C20, C25",2.2 uF,CGA3E1X7S1C225M080AC
12,2,12,"C21, C26",22nF,AC0402KRX7R7BB223
13,2,12,"C23, C28",10nF,GRT155R71C103KE01J
14,25,150,"D1, D2, D3, D4, D5, D6, D7, D8, D9, D10, D11, D14, D15, D16, D17, D18, D19, D20, D21, D22, D23, D24, D25, D26, D27",TVS,ESD321DPYR
15,1,3,D28,LTST-C193KRKT-5A,LTST-C193KRKT-5A
16,3,9,"EXT1, EXT2, EXT3",Male Conn.,14562042
17,1,3,EXT4,Male Connector,1-353293-6
18,1,3,EXT5,Photodiodes (8),SFH 203 P
19,1,3,EXT6,PWR Banana Plugs,1325-02
20,1,3,EXT7,Power Male Connector,3-640427-2
21,2,6,"EXT8, EXT9",Male MTR Conn.,14562042
22,1,3,EXT10,NiCr Wire Connector,3-640427-2
24,1,3,IC1,TPS25940LRVCR,TPS25940LRVCR
25,1,3,IC2,LP5912Q3.3DRVRQ1,LP5912Q3.3DRVRQ1
26,1,3,J1,Conn_02x08_Odd_Even,3-1734506-1
27,3,9,"J2, J3, J5",70543-0108,70543-0108
28,1,3,J4,Conn_01x05,2PH1-10-UA-SMT-A
29,1,3,J6,Conn_01x16,1-292230-6
30,2,6,"J7, J11",105431-1202,105431-1202
31,1,3,J8,10103594-0001LF,10103594-0001LF
32,2,6,"J9, J10",171973-0004,171973-0004
34,1,3,JP1,Jumper_3_Open,2PH1-10-UA-SMT-A
35,1,3,L1,220 nH,IHLP1212AEERR22M11
36,2,6,"Q1, Q2",NVR5198NLT1G,NVR5198NLT1G
37,1,3,Q3,IRLML6244TRPBF,IRLML6244TRPBF
38,4,24,"R1, R2, R5, R31",4.7k,AC0402FR-134K7L
39,2,12,"R3, R28",200k,AC0603FR-07200KL
40,1,6,R4,16.8k,AC0402FR-0716K9L
41,6,36,"R6, R8, R18, R26, R29, R30",100k,RMCF0402FT100K
42,1,6,R7,374k,RC0402FR-07374KL
43,1,6,R9,147k,RC0402FR-07147KL
44,1,6,R10,300k,RC0402JR-07300KL
45,1,6,R11,15k,AC0603FR-0715KL
46,2,12,"R12, R20",2.2k,AC0402FR-072K2L
47,6,36,"R13, R14, R15, R21, R22, R23",18k,AC0402FR-0718KL
48,4,24,"R16, R17, R24, R25",330m,KRL1632E-M-R330-F-T5
49,2,12,"R19, R27",1k,AC0402FR-131KL
50,1,6,R32,270,CRGCQ0402F270R
51,1,3,S1,KSR253GLFG,KSR253GLFG
53,1,3,U1,STM32L476RGTx,STM32L476RGT3
54,1,3,U2,CD4051B,CD4051BQPWRG4Q1
55,1,3,U3,LM321,LM321LVIDBVR
56,2,6,"U4, U5",NCV68261MTWAITBG,NCV68261MTWAITBG
57,2,6,"U6, U7",STSPIN220,STSPIN220
58,1,3,U8,TPS62867RQYR,TPS62867RQYR
59,1,3,U11,USBLC6-2SC6,USBLC6-2SC6
60,1,3,Y1,ECS_Chrystal_,ECS-160-8-36Q-AES-TR
